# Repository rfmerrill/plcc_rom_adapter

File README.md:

# plcc_rom_adapter
Adapter from 39SF040 to 27C800

OSH park project here: https://oshpark.com/shared_projects/aCNnlI0s

FUNCTIONALITY AND COMPLETENESS OF THIS REPO IS NOT GUARANTEED -- I DON'T REMEMBER HOW OLD SOME OF THE FILES ARE

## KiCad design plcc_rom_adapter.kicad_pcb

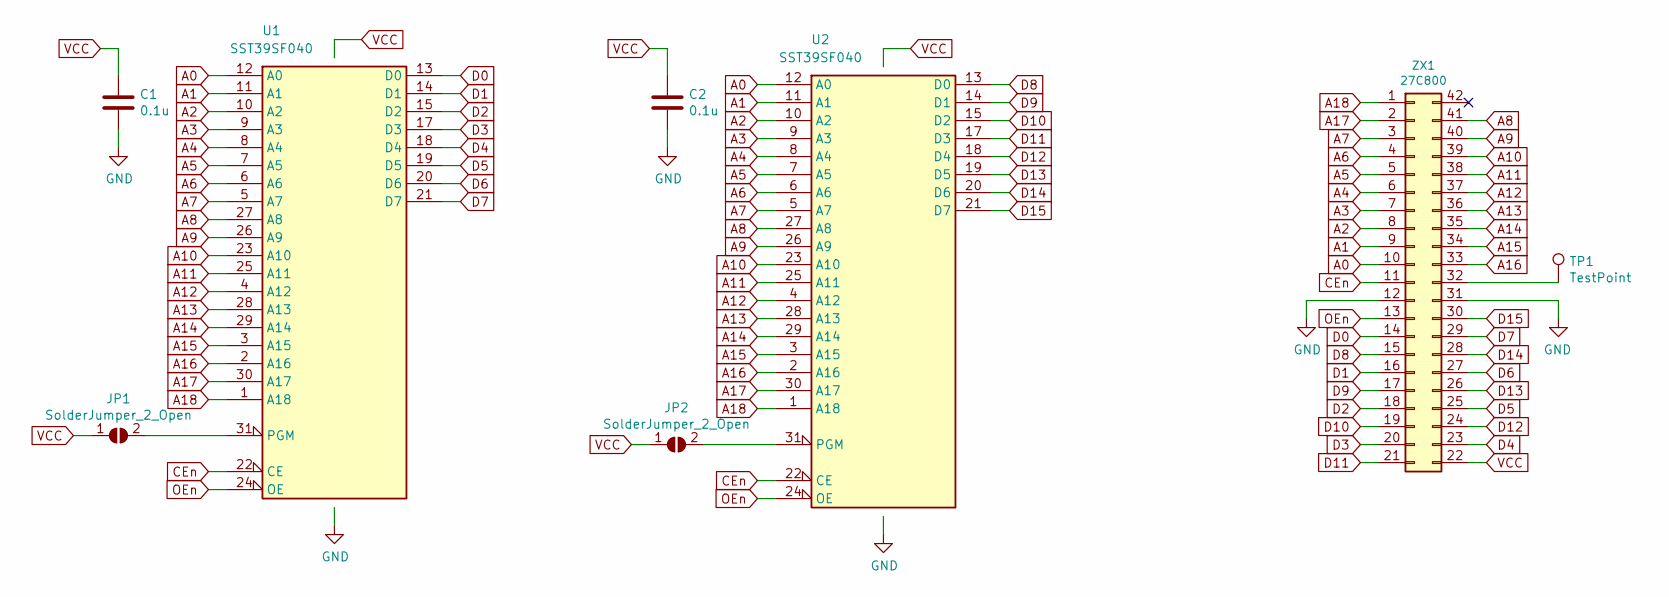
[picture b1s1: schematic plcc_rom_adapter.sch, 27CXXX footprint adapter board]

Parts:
C1, C2: 0.1u; C_0805_2012Metric_Pad1.15x1.40mm_HandSolder
JP1, JP2: SolderJumper_2_Open; SolderJumper-2_P1.3mm_Open_RoundedPad1.0x1.5mm
TP1: TestPoint; TestPoint_Pad_1.0x1.0mm
U1, U2: SST39SF040; PLCC-32_11.4x14.0mm_P1.27mm
ZX1: 27C800; DIP-42_W15.24mm_flipped

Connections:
A0: U1.12 (A0), U2.12 (A0), ZX1.10
A1: U1.11 (A1), U2.11 (A1), ZX1.9
A2: U1.10 (A2), U2.10 (A2), ZX1.8
A3: U1.9 (A3), U2.9 (A3), ZX1.7
A4: U1.8 (A4), U2.8 (A4), ZX1.6
A5: U1.7 (A5), U2.7 (A5), ZX1.5
A6: U1.6 (A6), U2.6 (A6), ZX1.4
A7: U1.5 (A7), U2.5 (A7), ZX1.3
A8: U1.27 (A8), U2.27 (A8), ZX1.41
A9: U1.26 (A9), U2.26 (A9), ZX1.40
A10: U1.23 (A10), U2.23 (A10), ZX1.39
A11: U1.25 (A11), U2.25 (A11), ZX1.38
A12: U1.4 (A12), U2.4 (A12), ZX1.37
A13: U1.28 (A13), U2.28 (A13), ZX1.36
A14: U1.29 (A14), U2.29 (A14), ZX1.35
A15: U1.3 (A15), U2.3 (A15), ZX1.34
A16: U1.2 (A16), U2.2 (A16), ZX1.33
A17: U1.30 (A17), U2.30 (A17), ZX1.2
A18: U1.1 (A18), U2.1 (A18), ZX1.1
CEn: U1.22 (CE), U2.22 (CE), ZX1.11
D0: U1.13 (D0), ZX1.14
D1: U1.14 (D1), ZX1.16
D2: U1.15 (D2), ZX1.18
D3: U1.17 (D3), ZX1.20
D4: U1.18 (D4), ZX1.23
D5: U1.19 (D5), ZX1.25
D6: U1.20 (D6), ZX1.27
D7: U1.21 (D7), ZX1.29
D8: U2.13 (D0), ZX1.15
D9: U2.14 (D1), ZX1.17
D10: U2.15 (D2), ZX1.19
D11: U2.17 (D3), ZX1.21
D12: U2.18 (D4), ZX1.24
D13: U2.19 (D5), ZX1.26
D14: U2.20 (D6), ZX1.28
D15: U2.21 (D7), ZX1.30
GND: C1.2, C2.2, U1.16 (GND), U2.16 (GND), ZX1.12, ZX1.31
unnamed: JP1.2 (B), U1.31 (PGM)
unnamed: JP2.2 (B), U2.31 (PGM)
unnamed: TP1.1, ZX1.32
OEn: U1.24 (OE), U2.24 (OE), ZX1.13
VCC: C1.1, C2.1, JP1.1 (A), JP2.1 (A), U1.32 (VCC), U2.32 (VCC), ZX1.22

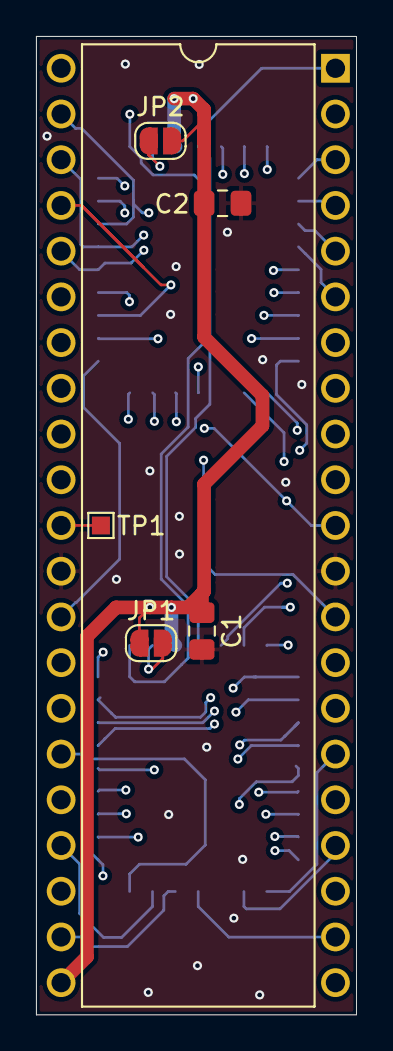
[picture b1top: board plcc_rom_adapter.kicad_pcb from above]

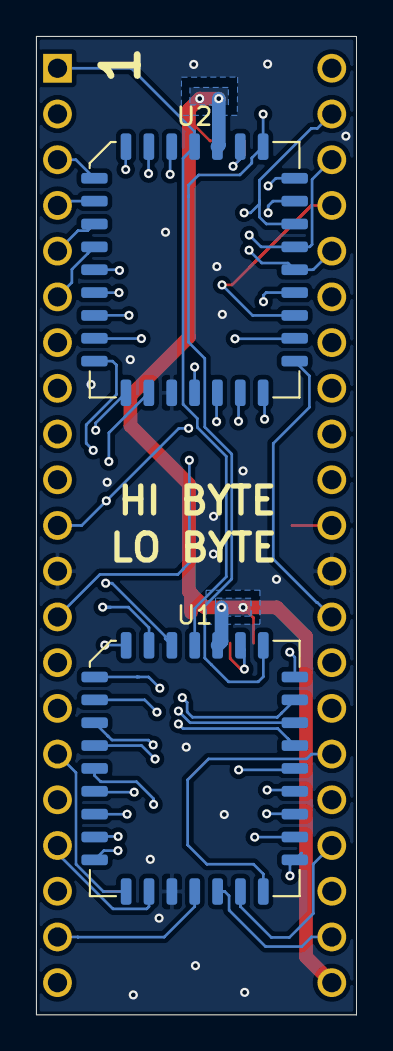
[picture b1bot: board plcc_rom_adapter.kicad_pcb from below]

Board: 4 copper layers, 17.8 x 54.4 mm, 8 parts (2 on the bottom side), 42 nets.

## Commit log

2021-10-11 Add Disclaimer
2021-10-11 Oops wrong link
